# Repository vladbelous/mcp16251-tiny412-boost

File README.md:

# "Programmable" MCP16251 boost converter with Attiny412 control

PCB for MCP16251 ([datasheet](http://ww1.microchip.com/downloads/en/devicedoc/20005173b.pdf)) voltage boost regulator, made "smarter" by the addition of a small ATTINY412 MCU:
* MCU's pin PA7 controls EN input pin of the boost regulator, allowing a very low power "sleep" / stand-by.
* Pin PA6 can be used to measure input voltage (VBAT). This can be used to protect battery from over-discharge.
* UPDI pin is broken out for programming arbitrary user-defined control logic.
* TXD/RXD (UART) pins are broken out for communication with downstream components (e.g. ones powered from the boost output), or just for debugging.
* A user-defined button (3mm x 6mm) pulls PA0/UPDI pin low when pressed. Note that PA0/UPDI pin *can* be used for input.

The MCU is powered through a ultra-low quiescent current 2.5V LDO (AP7354 with 0.6uA max quiescent).
TXB0104 is used for voltage level shifting. MIC809 voltage supervisor ensures TXB0104 is enabled only when VCCB > VCCA.

## Schematic:

## Layout:
Two-layer PCB with all components on front layer.

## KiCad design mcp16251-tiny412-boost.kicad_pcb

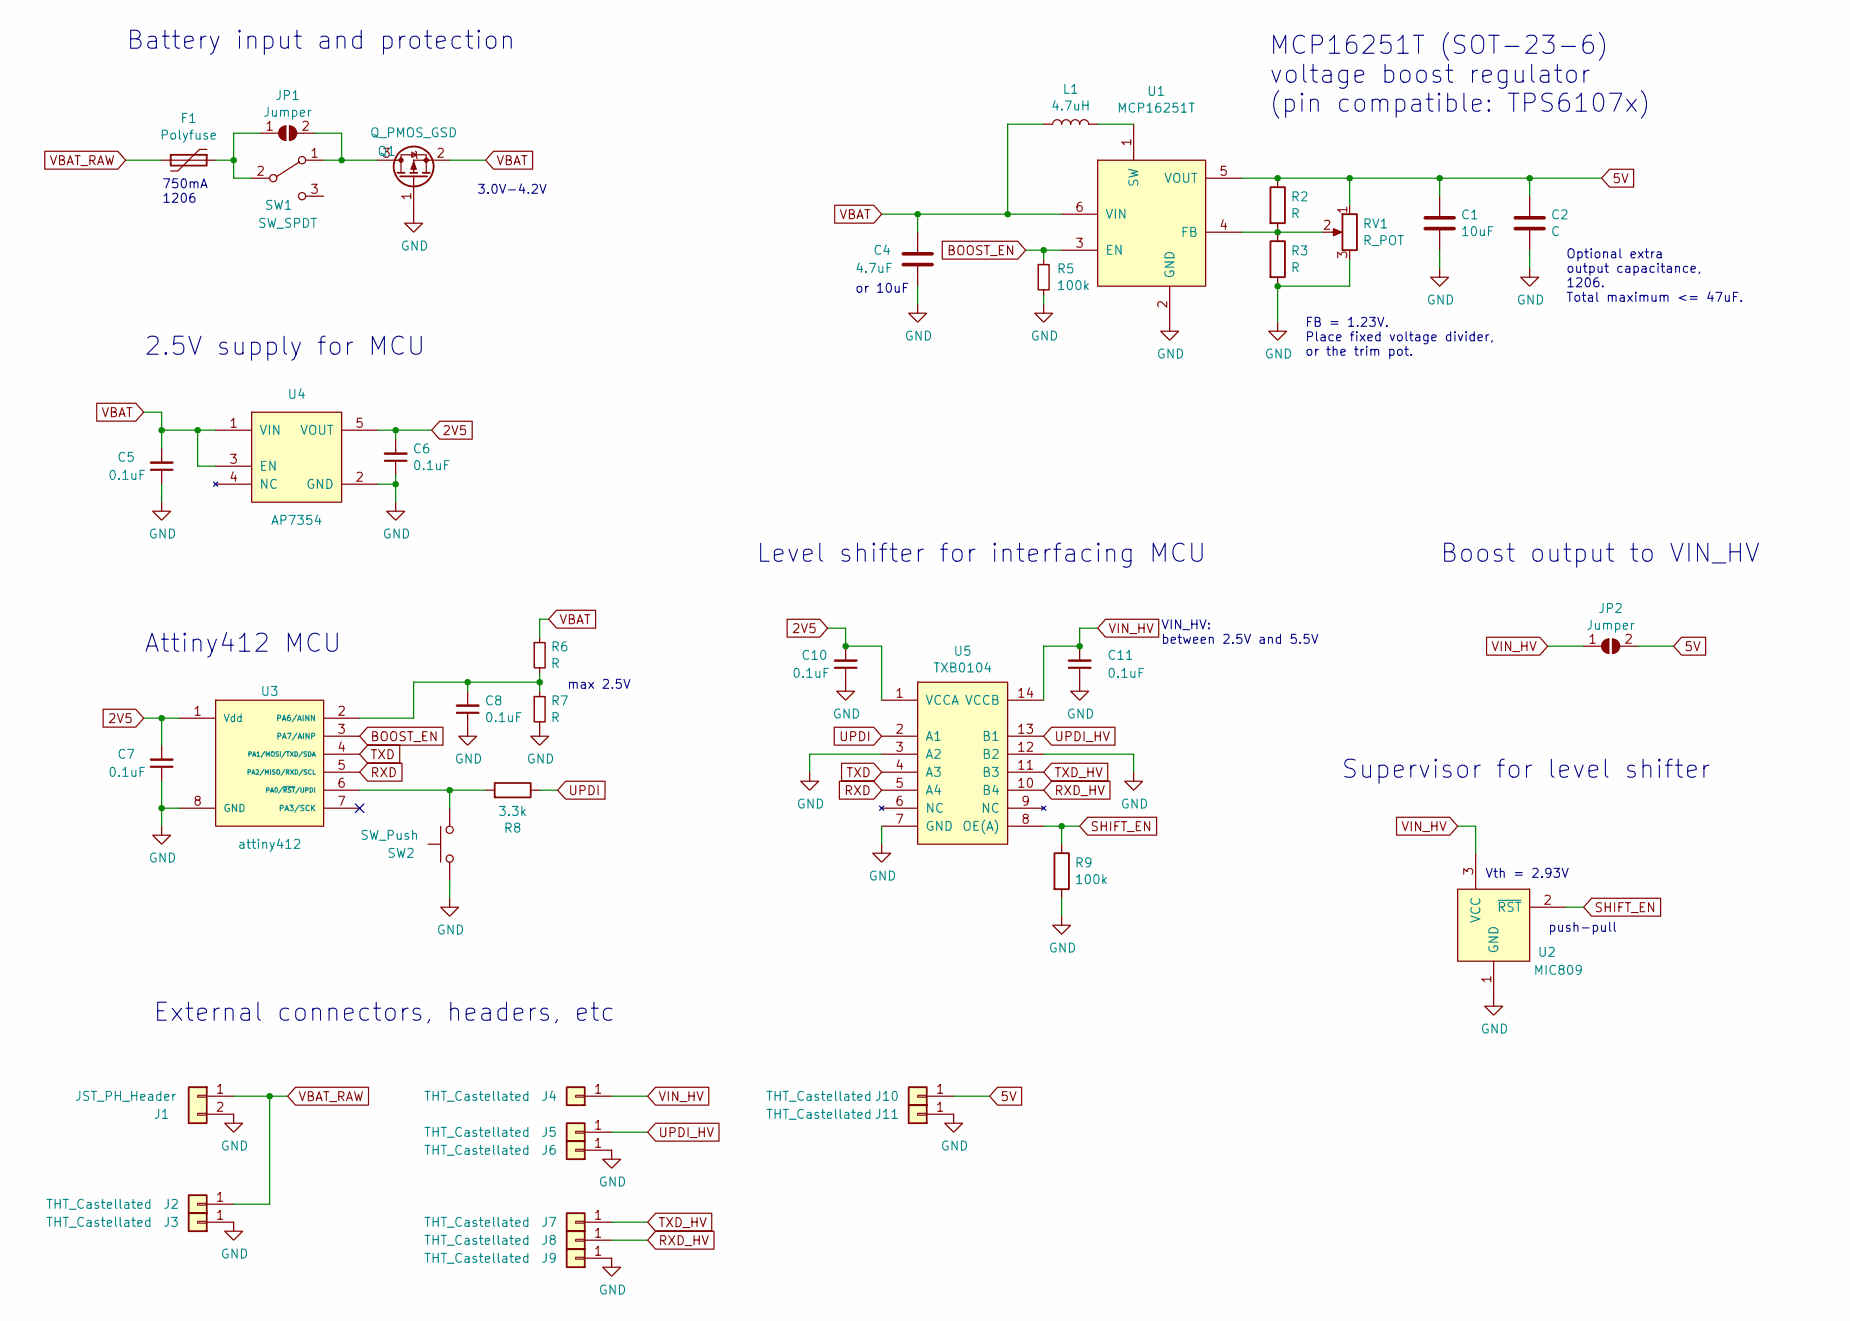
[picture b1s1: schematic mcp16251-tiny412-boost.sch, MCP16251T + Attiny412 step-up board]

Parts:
C1: 10uF; 1206_HS
C2: C; 1206_HS
C4: 4.7uF; 1206_HS
C5, C6, C7, C8, C10, C11: 0.1uF; 0805_HS
F1: Polyfuse; 1206_HS
J1: JST_PH_Header; JST_PH_S2B-PH-K_02x2.00mm_Angled
J2, J3, J4, J5, J6, J7, J8, J9, J10, J11: THT_Castellated; Conn_01x01_cast
JP1, JP2: Jumper; 0805_HS
L1: 4.7uH; L_Taiyo-Yuden_NR-S-40xx_HS
Q1: Q_PMOS_GSD; SOT-23_HS
R2, R3, R6, R7: R; 0805_HS
R5, R9: 100k; 0805_HS
R8: 3.3k; 0805_HS
RV1: R_POT; Conn_01x03_small
SW1: SW_SPDT; Conn_01x03_small
SW2: SW_Push; SW_SPST_PUSH_6mm_3mm
U1: MCP16251T; SOT-23-6_HS
U2: MIC809; SOT-23_HS
U3: attiny412; SOIC-8_3.9x4.9mm_Pitch1.27_HSmm
U4: AP7354; SOT-23-5_HS
U5: TXB0104; SOIC-14_3.9x8.7mm_Pitch1.27mm_HS

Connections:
2V5: C6.2, C7.2, C10.2, U3.1 (Vdd), U4.5 (VOUT), U5.1 (VCCA)
5V: C1.1, C2.1, J10.1, JP2.2 (B), R2.1, RV1.1, U1.5 (VOUT)
BOOST_EN: R5.1, U1.3 (EN), U3.3 (PA7/AINP)
GND: C1.2, C2.2, C4.2, C5.1, C6.1, C7.1, C8.1, C10.1, C11.1, J1.2, J3.1, J6.1, J9.1, J11.1, Q1.1 (G), R3.2, R5.2, R7.2, R9.2, RV1.3, SW2.2, U1.2 (GND), U2.1 (GND), U3.8 (GND), U4.2 (GND), U5.3 (A2), U5.7 (GND), U5.12 (B2)
unnamed: C8.2, R6.2, R7.1, U3.2 (PA6/AINN)
unnamed: F1.1, JP1.1 (A), SW1.2 (B)
unnamed: JP1.2 (B), Q1.3 (D), SW1.1 (A)
unnamed: L1.2, U1.1 (SW)
unnamed: R2.2, R3.1, RV1.2, U1.4 (FB)
unnamed: R8.2, SW2.1, U3.6 (PA0/~RST~/UPDI)
RXD: U3.5 (PA2/MISO/RXD/SCL), U5.5 (A4)
RXD_HV: J8.1, U5.10 (B4)
SHIFT_EN: R9.1, U2.2 (~RST), U5.8 (OE(A))
TXD: U3.4 (PA1/MOSI/TXD/SDA), U5.4 (A3)
TXD_HV: J7.1, U5.11 (B3)
UPDI: R8.1, U5.2 (A1)
UPDI_HV: J5.1, U5.13 (B1)
VBAT: C4.1, C5.2, L1.1, Q1.2 (S), R6.1, U1.6 (VIN), U4.1 (VIN), U4.3 (EN)
VBAT_RAW: F1.2, J1.1, J2.1
VIN_HV: C11.2, J4.1, JP2.1 (A), U2.3 (VCC), U5.14 (VCCB)

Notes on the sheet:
Battery input and protection
FB = 1.23V. Place fixed voltage divider, or the trim pot.
MCP16251T (SOT-23-6) voltage boost regulator (pin compatible: TPS6107x)
or 10uF
Optional extra output capacitance, 1206. Total maximum <= 47uF.
Vth = 2.93V
750mA 1206
push-pull
3.0V-4.2V
max 2.5V
2.5V supply for MCU
Attiny412 MCU
External connectors, headers, etc
Level shifter for interfacing MCU
VIN_HV: between 2.5V and 5.5V
Boost output to VIN_HV
Supervisor for level shifter

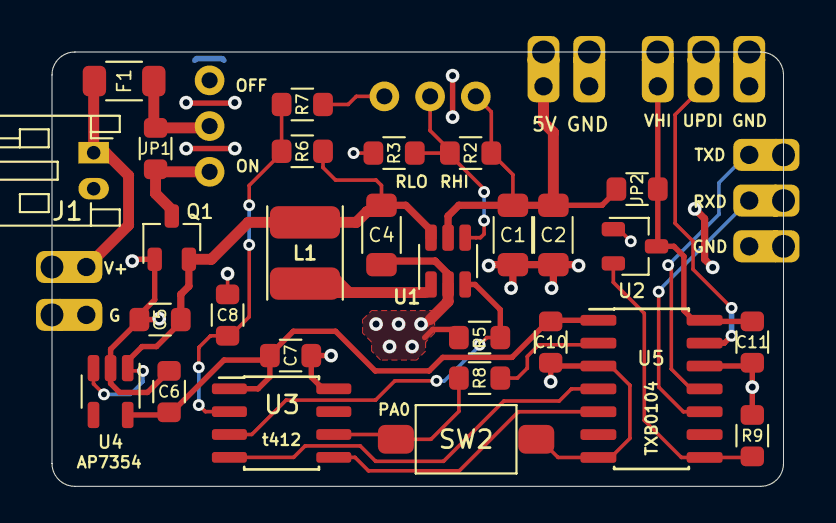
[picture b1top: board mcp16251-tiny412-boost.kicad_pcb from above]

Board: 2 copper layers, 40.6 x 24.1 mm, 40 parts (0 on the bottom side), 20 nets.

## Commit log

2019-01-22 Major components
2019-02-19 Further schematic work
2019-02-19 Add logic level shifter TXB104
2019-02-19 Initial complete design, needs proof-reading
2019-02-25 Annotate schematic, prepare footprints
2019-02-25 Prepare for layout
2019-02-26 Approx boost circuit arrangement
2019-02-27 Complete layout candidate, no routing
2019-03-01 Step-up converter sub-circuit wiring
2019-03-01 Complete routing, pending verification
2019-03-02 Check layout, add silkscreen
2019-03-04 Improve readme, add images

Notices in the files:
mcp16251-tiny412-boost.kicad_pcb:
CC BY-SA 4.0 license
CC BY-SA 4.0
mcp16251-tiny412-boost.sch:
creativecommons.org/licenses
